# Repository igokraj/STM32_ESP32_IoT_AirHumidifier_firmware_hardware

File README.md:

# STM32 + ESP32 IoT (AWS Core) Air Humidifier

Projekt zakładał stworzenie sterownika nawilżacza powietrza opartego na dwóch mikrokontrolerach STM32F446RE oraz ESP32-S3. STM32 odpowiada za sterowanie wentylatorem sygnałem PWM, obsługę czujników oraz maszynę stanów, na której opiera się działanie systemu. ESP32 służy wyłącznie do połączenia urządzenia z Wi-Fi, a następnie chmurą AWS IoT Core (Amazon) poprzez protokół MQTT.

Oba mikrokontrolery komunikują się ze sobą przez UART, wymieniając wiadomości w formacie JSON. STM32 wysyła do ESP32 informacje o aktualnej wilgotności, stanie systemu, prędkości obrotowej wentylatora oraz progu wilgotności ustawionym przez użytkownika. ESP32 przekazuje do STM32 wiadomość JSON przygotowaną wcześniej przez użytkownika, zawierającą żądany próg wilgotności w pomieszczeniu (np. 60%) oraz żądaną prędkość wentylatora, wybieraną poziomami od 0 do 5. Każdy poziom odpowiada innemu wypełnieniu sygnału PWM.

Firmware na STM32 jest napisany w C++, natomiast ESP32 działa na FreeRTOS, który jest natywną częścią frameworka.

Projekt był testowany na płytce stykowej, bez rzeczywistego wentylatora. Pomiar prędkości obrotowej sprawdzałem za pomocą drugiego timera, który generował impulsy i był fizycznie połączony z wejściem timera zliczającego impulsy z wentylatora. Sterowanie wentylatorem testowałem na servo ze zmienionymi parametrami sygnału PWM, ale logika sterowania pozostała taka sama.

This is an air humidifier controller built around two microcontrollers: an STM32F446RE and an ESP32-S3. The STM32 does the actual work. It drives the fan with PWM, reads the sensors and runs the state machine the whole system is based on. The ESP32 has only one job: it connects to Wi-Fi and talks to AWS IoT Core over MQTT.

The two chips talk to each other over UART using JSON messages. The STM32 sends the current humidity, system state, fan RPM and the humidity target set by the user. The ESP32 sends back a JSON message from the user with the target room humidity (e.g. 60%) and the fan speed level, from 0 to 5. Each level is a different PWM duty cycle.

The STM32 firmware is written in C++. The ESP32 runs on FreeRTOS, which comes built into ESP-IDF.

I tested everything on a breadboard without a real fan. To check the RPM measurement, I used a second timer to generate pulses and wired it to the input of the timer that counts the fan pulses. For fan control I used a servo instead, with different PWM settings, but the control logic stayed the same.

## Photos

**Breadboard prototype**

**Schematic**

**PCB layout and 3D render**

<p align="center">
  
  &nbsp;
  
</p>

## How it works

The system has four states: **Waiting**, **Running**, **EmptyContainer** (no water in the tank) and **Error**.

In the main loop the STM32:

1. checks for a JSON command from the ESP32 (`{"hum": 55, "rpm_lvl": 3}`) and updates the target humidity and fan speed level,
2. reads humidity from the HTU21D every 1 s. After 3 failed reads in a row it resets the I2C bus and goes into Error,
3. reads the water level sensor (float switch),
4. sets the state. Priority: sensor fault, then empty tank, then humidity below target,
5. drives the fan (PWM) and the RGB LED (green: running, blue: empty tank, red: error),
6. every 10 s sends a status message to the ESP32, for example `{"CurrentHumidity":48.20,"SetHum":70.00,"Status":1,"RPM":2000}`.

Fan speed has 6 levels (0 to 5, which means 0 to 100% PWM). The real RPM is measured from the fan's tachometer output using timer input capture. The watchdog (IWDG) resets the MCU if the program hangs.

The ESP32 passes messages between UART (115200 baud) and MQTT (TLS):

- publishes to `humidifier/<client_id>/data`
- subscribes to `humidifier/<client_id>/cmd` (only valid JSON is sent on to the STM32)

## Peripherals / electronics

- **STM32F446RETx**: main microcontroller
- **ESP32-S3-WROOM-1**: Wi-Fi / MQTT module
- **HTU21D**: humidity sensor (I2C)
- **4-pin PWM fan** (PC fan, e.g. Noctua NF-A6x25 PWM): 12 V, PWM and tachometer
- **Water level sensor** (float switch)
- **RGB LED**: shows the system state
- **AMS1117-3.3**: 3.3 V voltage regulator
- 12 V power connector (barrel jack) with a fuse, reverse polarity diode and TVS overvoltage protection
- SWD connector (ST-Link) for the STM32 and UART/boot header for programming the ESP32

## BOM (short version)

| Reference        | Component                                             | Qty |
| ---------------- | ----------------------------------------------------- | --- |
| U2               | STM32F446RETx                                         | 1   |
| U3               | ESP32-S3-WROOM-1                                      | 1   |
| U1               | AMS1117-3.3 (3.3 V regulator)                         | 1   |
| RGB1             | RGB LED                                               | 1   |
| LED1             | LED (power indicator)                                 | 1   |
| J1               | Power jack (barrel jack)                              | 1   |
| J2               | 4-pin PWM fan connector                               | 1   |
| J3               | Screw terminal (water level sensor)                   | 1   |
| J4               | ESP32 programming header                              | 1   |
| J5               | HTU21D connector                                      | 1   |
| STLink1          | STM32 programmer connector                            | 1   |
| F1               | Fuse                                                  | 1   |
| D1               | Schottky diode B340 (reverse polarity protection)     | 1   |
| D2               | TVS diode SMBJ15A (overvoltage protection)            | 1   |
| L1               | Ferrite bead (power filtering)                        | 1   |
| R, C             | Resistors and capacitors (filtering, pull-up/down)    | ~28 |

The full list (with LCSC part numbers) is in `AirHumidifier/hardware/BOM.xlsx` and `All_BOM.csv`.

## Firmware

**STM32**: written in **C++** on top of the C code generated by STM32CubeMX/HAL. The humidifier state logic, humidity sensor, UART, JSON parser and I2C bus recovery are separate classes/modules. The rest (GPIO, I2C, timers, UART, watchdog) is generated HAL code.

**ESP32**: written in **C** with ESP-IDF (FreeRTOS), split into `WIFI`, `UART` and `MQTT` modules. To build it you have to add your own `main/secrets.h` (Wi-Fi credentials, AWS endpoint and client ID) and AWS IoT certificates in `main/Cert/`. They are not included in the repo.

## Repo structure

- `AirHumidifier/firmware/stm32/`: CMake project with the STM32 sources
- `AirHumidifier/firmware/esp32/`: ESP-IDF project for the ESP32
- `AirHumidifier/hardware/`: KiCad schematic and PCB, production files (Gerbers), BOM
- `AirHumidifier/hardware/Images/`: schematic and PCB renders

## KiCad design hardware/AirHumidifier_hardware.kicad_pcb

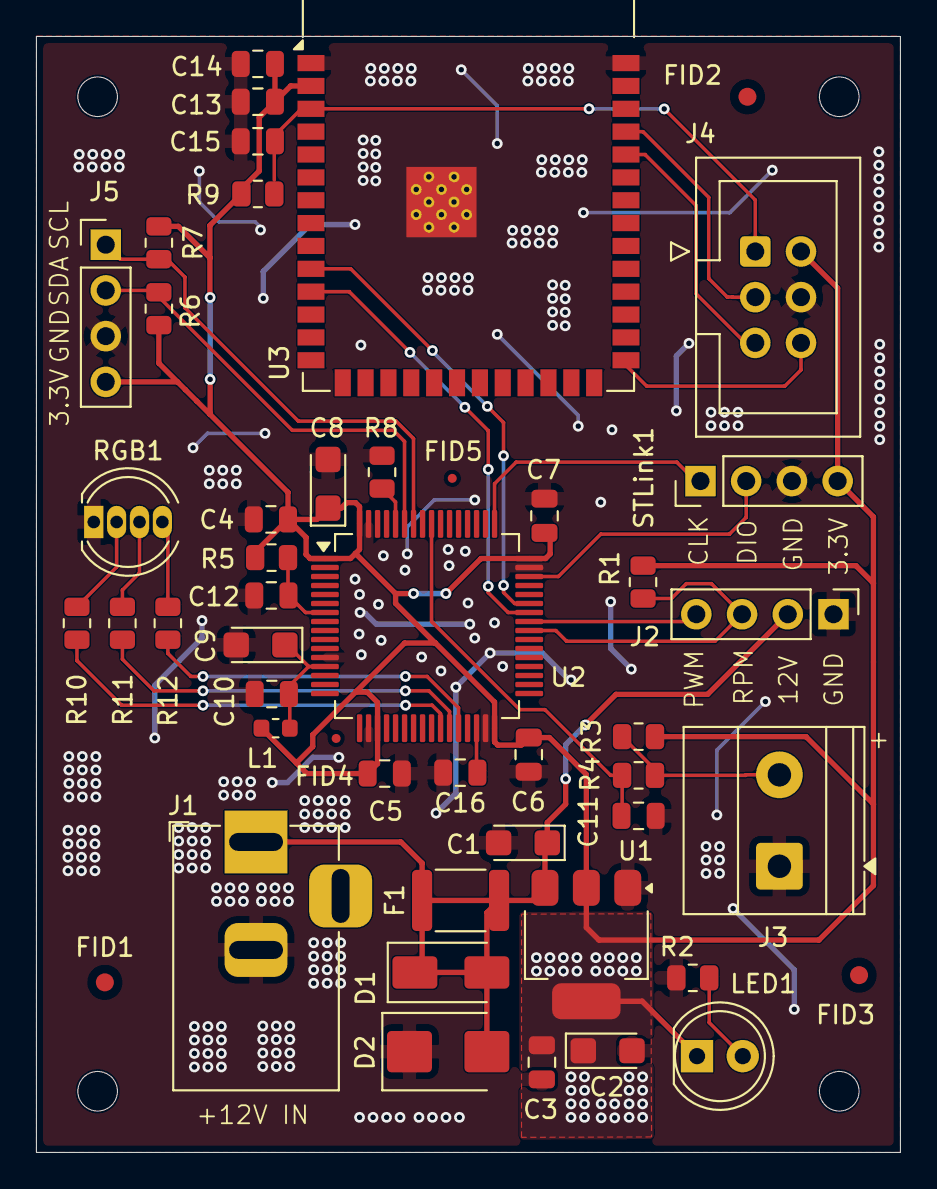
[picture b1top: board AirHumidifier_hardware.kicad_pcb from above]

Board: 2 copper layers, 48.0 x 62.0 mm, 52 parts (0 on the bottom side), 28 nets.

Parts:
C1, C2: 10uF; CP_EIA-3216-18_Kemet-A
C3, C4, C5, C6, C7, C10, C11, C12, C14: 100nF; C_0805_2012Metric
C8: 4.7uF; CP_EIA-3216-18_Kemet-A
C9: 1uF; CP_EIA-3216-18_Kemet-A
C13: 22uF; C_0805_2012Metric
C15: 1uF; C_0805_2012Metric
C16: 4.7uF; C_0805_2012Metric
D1: B340_SMA; D_SMA
D2: SMBJ15A; D_SMB
F1: 1812L150/24; Fuse_1812_4532Metric
FID1, FID2, FID3: Fiducial; Fiducial_1mm_Mask2mm
FID4, FID5: Fiducial; Fiducial_0.5mm_Mask1mm
H1, H2, H3, H4: MountingHole; MountingHole_2.2mm_M2
J1: Barrel_Jack; BarrelJack_Horizontal
J2, J5: Conn_01x04_Pin; PinHeader_1x04_P2.54mm_Vertical
J3: Screw_Terminal_01x02; TerminalBlock_Phoenix_MKDS-1,5-2-5.08_1x02_P5.08mm_Horizont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
J4: Conn_02x03_Odd_Even; IDC-Header_2x03_P2.54mm_Vertical
L1: BEAD(FCM1608KF-601T03); L_0603_1608Metric
LED1: LED; LED_D5.0mm
R1: 2.2k; R_0805_2012Metric
R2, R10, R11, R12: 330; R_0805_2012Metric
R3, R5, R8, R9: 10k; R_0805_2012Metric
R4: 1k; R_0805_2012Metric
R6, R7: 4.7k; R_0805_2012Metric
RGB1: LED_ARGB; LED_D5.0mm-4_RGB
STLink1: Conn_01x04_Pin; PinHeader_1x04_P2.54mm_Vertical
U1: AMS1117-3.3_SOT223; SOT-223-3_TabPin2
U2: STM32F446RETx; LQFP-64_10x10mm_P0.5mm
U3: ESP32-S3-WROOM-1

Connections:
+12V: C1.1, D1.1 (K), D1.2 (A), D2.2 (A2), F1.1, F1.2, J1.1, J2.2, U1.3 (VI)
Blue_LED: R12.2, U2.28 (PB2)
ESP_EN: C15.1, J4.1, R9.2, U3.3 (EN)
ESP_I00: J4.6, U3.27 (IO0)
GND: C1.2, C2.2, C3.2, C4.2, C5.2, C6.2, C7.2, C8.2, C9.2, C10.2, C11.2, C12.2, C13.2, C14.2, C15.2, C16.2, D2.1 (A1), J1.2, J2.1, J3.1, J4.4, J5.3, R2.1, R8.1, RGB1.1 (A), STLink1.3, U1.1 (GND), U2.12 (VSSA), U2.18 (VSS), U2.31 (VSS), U2.47 (VSS), U2.63 (VSS), U3.1 (GND), U3.40 (GND), U3.41 (GND)
Green_LED: R11.2, U2.27 (PB1)
I2C_SCL: J5.1, R7.2, U2.58 (PB6)
I2C_SDA: J5.2, R6.2, U2.59 (PB7)
unnamed: J3.2, R3.2, R4.1
unnamed: LED1.2 (A), R2.2
unnamed: R12.1, RGB1.4 (BK)
unnamed: R11.1, RGB1.3 (GK)
unnamed: R10.1, RGB1.2 (RK)
unnamed: R8.2, U2.60 (BOOT0)
unnamed: C12.1, R5.2, U2.7 (NRST)
unnamed: C16.1, U2.30 (VCAP_1)
PWM: J2.4, U2.41 (PA8)
RPM: J2.3, R1.2, U2.40 (PC9)
RXD0: J4.5, U3.36 (RXD0)
Red_LED: R10.2, U2.26 (PB0)
SWCLK: STLink1.1, U2.49 (PA14)
SWDIO: STLink1.2, U2.46 (PA13)
TXD0: J4.3, U3.37 (TXD0)
USART1_RX: U2.43 (PA10), U3.10 (IO17)
USART1_TX: U2.42 (PA9), U3.11 (IO18)
VDDA: C9.1, C10.1, L1.2, U2.13 (VDDA)
VDD_MCU: C2.1, C3.1, C4.1, C5.1, C6.1, C7.1, C8.1, C13.1, C14.1, J4.2, J5.4, L1.1, LED1.1 (K), R1.1, R3.1, R5.1, R6.1, R7.1, R9.1, STLink1.4, U1.2 (VO), U2.1 (VBAT), U2.19 (VDD), U2.32 (VDD), U2.48 (VDD), U2.64 (VDD), U3.2 (3V3)
Water_level: C11.1, R4.2, U2.56 (PB4)

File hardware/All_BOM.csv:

Reference,Qty,Value,DNP,Exclude from BOM,Exclude from Board,Footprint,Datasheet
"C1,C2",2,10uF,,,,Capacitor_Tantalum_SMD:CP_EIA-3216-18_Kemet-A,
"C3,C4,C5,C6,C7,C10,C11,C12,C14",9,100nF,,,,Capacitor_SMD:C_0805_2012Metric,
C8,1,4.7uF,,,,Capacitor_Tantalum_SMD:CP_EIA-3216-18_Kemet-A,
C9,1,1uF,,,,Capacitor_Tantalum_SMD:CP_EIA-3216-18_Kemet-A,
C13,1,22uF,,,,Capacitor_SMD:C_0805_2012Metric,
C15,1,1uF,,,,Capacitor_SMD:C_0805_2012Metric,
C16,1,4.7uF,,,,Capacitor_SMD:C_0805_2012Metric,
D1,1,B340_SMA,,,,Diode_SMD:D_SMA,
D2,1,SMBJ15A,,,,Diode_SMD:D_SMB,
F1,1,1812L150/24,,,,Fuse:Fuse_1812_4532Metric,
J1,1,Barrel_Jack,,,,Connector_BarrelJack:BarrelJack_Horizontal,
"J2,J5,STLink1",3,Conn_01x04_Pin,,,,Connector_PinHeader_2.54mm:PinHeader_1x04_P2.54mm_Vertical,
J3,1,Screw_Terminal_01x02,,,,"TerminalBlock_Phoenix:TerminalBlock_Phoenix_MKDS-1,5-2-5.08_1x02_P5.08mm_Horizontal",
J4,1,Conn_02x03_Odd_Even,,,,Connector_IDC:IDC-Header_2x03_P2.54mm_Vertical,
L1,1,BEAD(FCM1608KF-601T03),,,,Inductor_SMD:L_0603_1608Metric,
LED1,1,LED,,,,LED_THT:LED_D5.0mm,
R1,1,2.2k,,,,Resistor_SMD:R_0805_2012Metric,
"R2,R10,R11,R12",4,330,,,,Resistor_SMD:R_0805_2012Metric,
"R3,R5,R8,R9",4,10k,,,,Resistor_SMD:R_0805_2012Metric,
R4,1,1k,,,,Resistor_SMD:R_0805_2012Metric,
"R6,R7",2,4.7k,,,,Resistor_SMD:R_0805_2012Metric,
RGB1,1,LED_ARGB,,,,LED_THT:LED_D5.0mm-4_RGB,
U1,1,AMS1117-3.3_SOT223,,,,Package_TO_SOT_SMD:SOT-223-3_TabPin2,http://www.advanced-monolithic.com/pdf/ds1117.pdf
U2,1,STM32F446RETx,,,,Package_QFP:LQFP-64_10x10mm_P0.5mm,https://www.st.com/resource/en/datasheet/stm32f446re.pdf
U3,1,ESP32-S3-WROOM-1,,,,RF_Module:ESP32-S3-WROOM-1,https://www.espressif.com/sites/default/files/documentation/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

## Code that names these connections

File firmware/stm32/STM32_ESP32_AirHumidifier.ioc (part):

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Mcu.Name=STM32F446R(C-E)Tx
Mcu.Package=LQFP64
Mcu.UserName=STM32F446RETx
PA10.Mode=Asynchronous
PA10.Signal=USART1_RX
PA13.GPIOParameters=GPIO_Label
PA13.GPIO_Label=TMS
PA13.Mode=Serial_Wire
PA13.Signal=SYS_JTMS-SWDIO
PA14.GPIOParameters=GPIO_Label
PA14.GPIO_Label=TCK
PA14.Mode=Serial_Wire
PA14.Signal=SYS_JTCK-SWCLK
PA2.GPIOParameters=GPIO_Label
PA2.GPIO_Label=USART_TX
PA2.Mode=Asynchronous
PA2.Signal=USART2_TX
PA3.GPIOParameters=GPIO_Label
PA3.GPIO_Label=USART_RX
PA3.Mode=Asynchronous
PA3.Signal=USART2_RX
PA5.GPIOParameters=GPIO_Label
PA5.GPIO_Label=LD2 [Green Led]
PA5.Signal=GPIO_Output
PA8.GPIOParameters=GPIO_Label
PA8.GPIO_Label=PWM
PA8.Signal=S_TIM1_CH1
PA9.Mode=Asynchronous
PA9.Signal=USART1_TX
PB0.GPIOParameters=GPIO_Label
PB0.GPIO_Label=Red_LED
PB0.Signal=GPIO_Output
PB1.GPIOParameters=GPIO_Label
PB1.GPIO_Label=Green_LED
PB1.Signal=GPIO_Output
PB2.GPIOParameters=GPIO_Label
PB2.GPIO_Label=Blue_LED
PB2.Signal=GPIO_Output
PB3.GPIOParameters=GPIO_Label
PB3.GPIO_Label=SWO
PB3.Signal=SYS_JTDO-SWO
PB4.GPIOParameters=GPIO_PuPd,GPIO_Label
PB4.GPIO_Label=Water_level
PB4.GPIO_PuPd=GPIO_PULLUP
PB4.Signal=GPIO_Input
PB6.GPIOParameters=GPIO_Pu
PB6.GPIO_Pu=GPIO_PULLUP
PB6.Mode=I2C
PB6.Signal=I2C1_SCL
PB7.GPIOParameters=GPIO_Pu
PB7.GPIO_Pu=GPIO_PULLUP
PB7.Mode=I2C
PB7.Signal=I2C1_SDA
PC13.GPIOParameters=GPIO_Label,GPIO_ModeDefaultEXTI
PC13.GPIO_Label=B1 [Blue PushButton]
PC13.GPIO_ModeDefaultEXTI=GPIO_MODE_IT_FALLING
PC13.Signal=GPXTI13
PC14-OSC32_IN.Mode=LSE-External-Oscillator
PC14-OSC32_IN.Signal=RCC_OSC32_IN
PC15-OSC32_OUT.Mode=LSE-External-Oscillator
PC15-OSC32_OUT.Signal=RCC_OSC32_OUT
PC9.GPIOParameters=GPIO_PuPd,GPIO_Label
PC9.GPIO_Label=RPM
PC9.GPIO_PuPd=GPIO_PULLUP
PC9.Signal=S_TIM3_CH4
PH0-OSC_IN.Mode=HSE-External-Oscillator
PH0-OSC_IN.Signal=RCC_OSC_IN
PH1-OSC_OUT.Mode=HSE-External-Oscillator
PH1-OSC_OUT.Signal=RCC_OSC_OUT
RCC.HSE_VALUE=8000000
RCC.SYSCLKFreq_VALUE=84000000
RCC.SYSCLKSource=RCC_SYSCLKSOURCE_PLLCLK
board=NUCLEO-F446RE
boardIOC=true
